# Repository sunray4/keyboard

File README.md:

# RayBoard

This custom iOS mechanical keyboard features:
- 95 switches in keyboard matrix
- 0.91" OLED display to indicate capslock and play simple animations
- Rotary Encoder Switch for volume/brightness control
- Self-designed 3D printed case (Fusion 360)
- Custom PCB (Kicad)
- KMK firmware
- Powered by Raspberry Pi Pico!!

## Video Demo
<a href="https://hc-cdn.hel1.your-objectstorage.com/s/v3/838ee69a4a7859cef761f4f2ce842302e564a838_rayboard_demo4.mp4" target="_blank">Demo Link</a>

## PCB
| **Schematic** |
|-----------|
||

| **PCB** |
|-----------|
||

| **3D Render** |
|-----------|
||
||

| **Case Design** |
|-----------|
||
||

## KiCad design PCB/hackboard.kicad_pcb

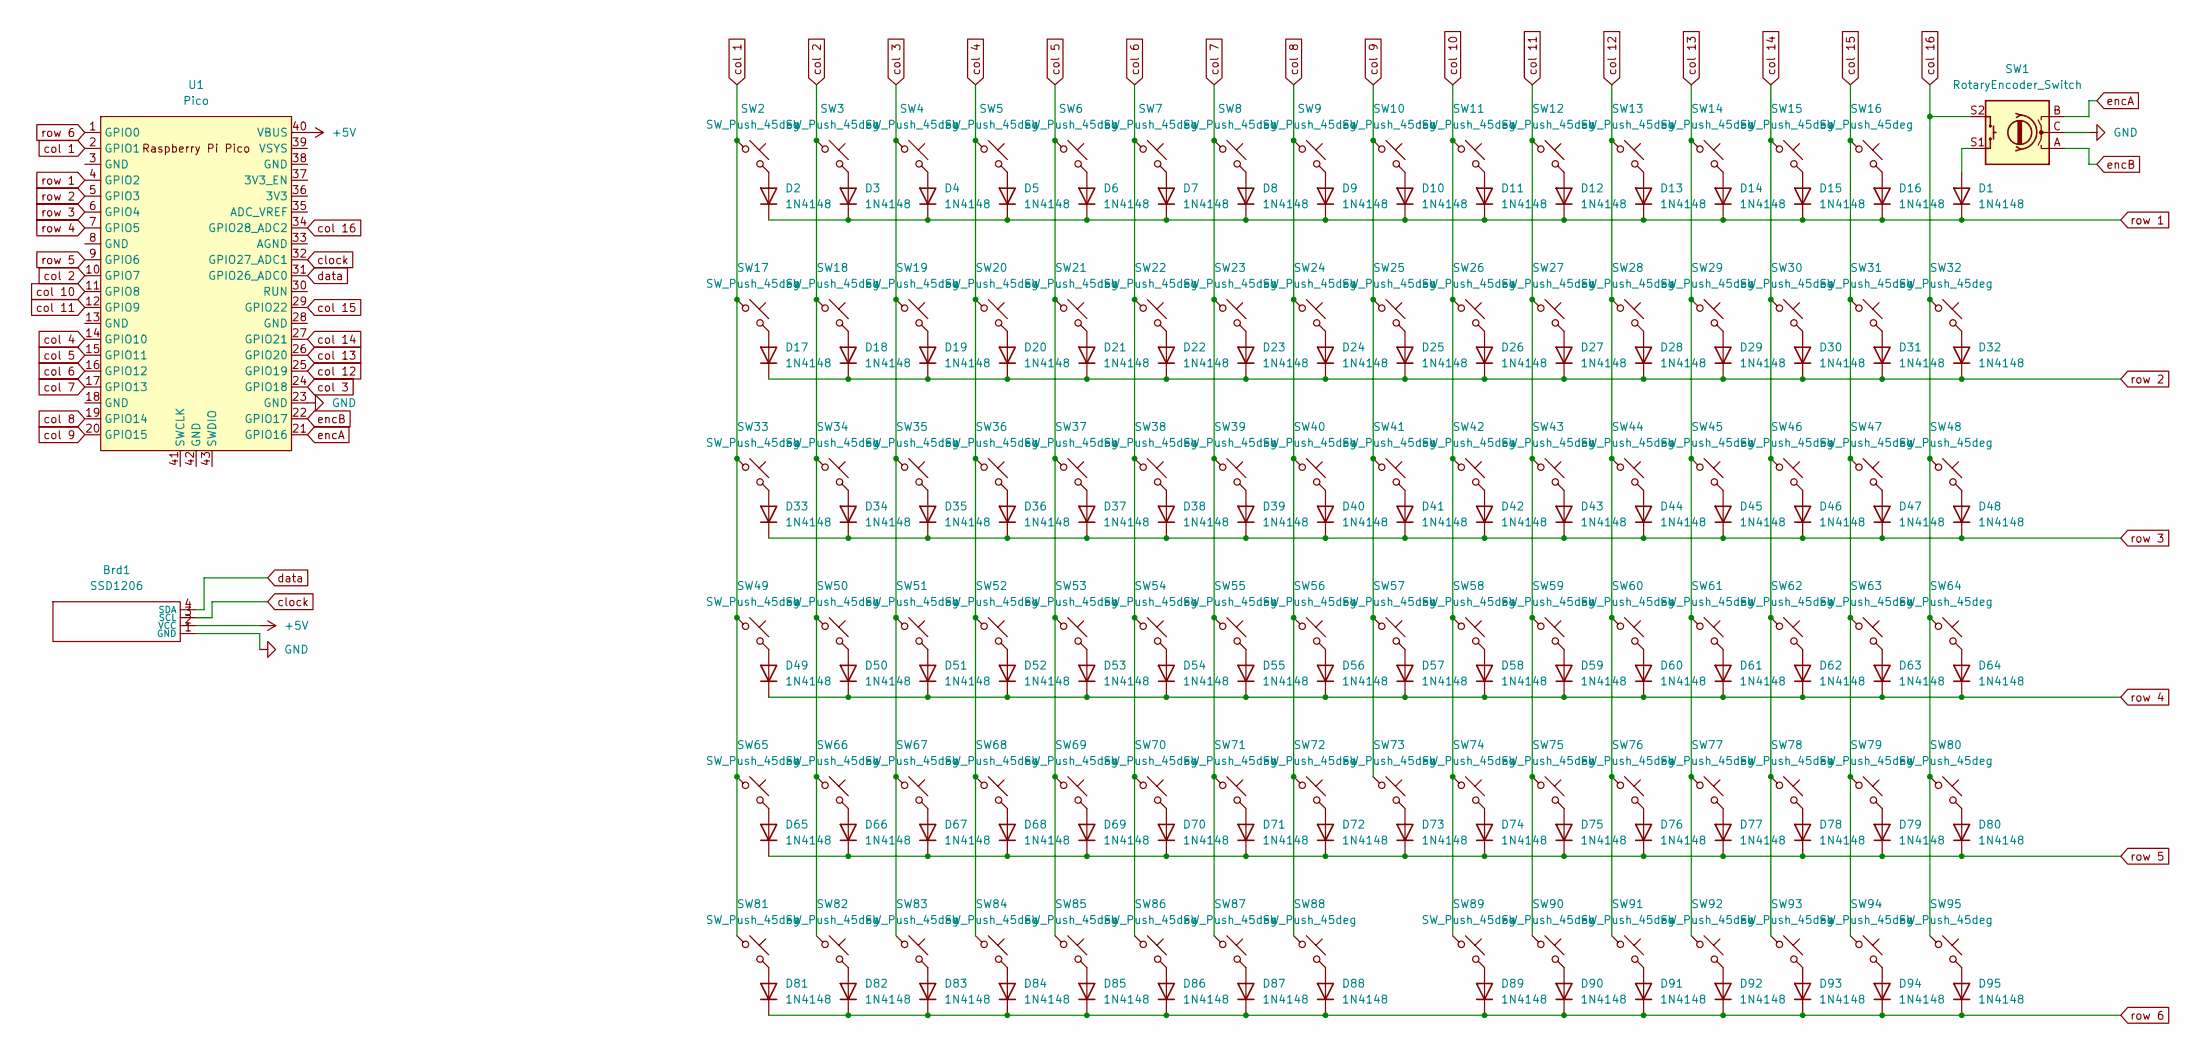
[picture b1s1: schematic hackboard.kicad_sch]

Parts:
Brd1: SSD1206; SSD1306-0.91-OLED-4pin-128x32
D1, D2, D3, D4, D5, D6, D7, D8, D9, D10, D11, D12, D13, D14, D15, D16, D17, D18, D19, D20, D21, D22, D23, D24, D25, D26, D27, D28, D29, D30, D31, D32, D33, D34, D35, D36, D37, D38, D39, D40, D41, D42, D43, D44, D45, D46, D47, D48, D49, D50, D51, D52, D53, D54, D55, D56, D57, D58, D59, D60, D61, D62, D63, D64, D65, D66, D67, D68, D69, D70, D71, D72, D73, D74, D75, D76, D77, D78, D79, D80, D81, D82, D83, D84, D85, D86, D87, D88, D89, D90, D91, D92, D93, D94, D95: 1N4148; D_SOD-123
SW1: RotaryEncoder_Switch; RotaryEncoder_Alps_EC11E-Switch_Vertical_H20mm
SW2, SW3, SW4, SW5, SW6, SW7, SW8, SW9, SW10, SW11, SW12, SW13, SW14, SW15, SW16, SW17, SW18, SW19, SW20, SW21, SW22, SW23, SW24, SW25, SW26, SW27, SW28, SW29, SW30, SW31, SW33, SW34, SW36, SW37, SW38, SW39, SW40, SW41, SW42, SW43, SW44, SW45, SW46, SW47, SW49, SW50, SW53, SW54, SW55, SW56, SW57, SW58, SW59, SW60, SW61, SW62, SW63, SW65, SW66, SW67, SW69, SW70, SW71, SW72, SW73, SW74, SW75, SW76, SW77, SW78, SW80, SW82, SW83, SW86, SW87, SW88, SW92, SW93, SW94, SW95: SW_Push_45deg; SW_Cherry_MX_1.00u_PCB
SW32, SW81: SW_Push_45deg; SW_Cherry_MX_2.00u_PCB
SW35, SW48: SW_Push_45deg; SW_Cherry_MX_1.50u_PCB
SW51, SW84: SW_Push_45deg; SW_Cherry_MX_2.00u_Vertical_PCB
SW52, SW79: SW_Push_45deg; SW_Cherry_MX_1.75u_PCB
SW64, SW68: SW_Push_45deg; SW_Cherry_MX_2.25u_PCB
SW85, SW90, SW91: SW_Push_45deg; SW_Cherry_MX_1.25u_PCB
SW89: SW_Push_45deg; SW_Cherry_MX_6.25u_PCB
U1: Pico; RaspberryPi_Pico_Common_THT

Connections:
+5V: Brd1.2 (VCC), U1.40 (VBUS)
GND: Brd1.1 (GND), SW1.C, U1.23 (GND)
unnamed: D1.2 (A), SW1.S1
unnamed: D2.2 (A), SW2.2
unnamed: D3.2 (A), SW3.2
unnamed: D4.2 (A), SW4.2
unnamed: D5.2 (A), SW5.2
unnamed: D6.2 (A), SW6.2
unnamed: D7.2 (A), SW7.2
unnamed: D8.2 (A), SW8.2
unnamed: D9.2 (A), SW9.2
unnamed: D10.2 (A), SW10.2
unnamed: D11.2 (A), SW11.2
unnamed: D12.2 (A), SW12.2
unnamed: D13.2 (A), SW13.2
unnamed: D14.2 (A), SW14.2
unnamed: D15.2 (A), SW15.2
unnamed: D16.2 (A), SW16.2
unnamed: D17.2 (A), SW17.2
unnamed: D18.2 (A), SW18.2
unnamed: D19.2 (A), SW19.2
unnamed: D20.2 (A), SW20.2
unnamed: D21.2 (A), SW21.2
unnamed: D22.2 (A), SW22.2
unnamed: D23.2 (A), SW23.2
unnamed: D24.2 (A), SW24.2
unnamed: D25.2 (A), SW25.2
unnamed: D26.2 (A), SW26.2
unnamed: D27.2 (A), SW27.2
unnamed: D28.2 (A), SW28.2
unnamed: D29.2 (A), SW29.2
unnamed: D30.2 (A), SW30.2
unnamed: D31.2 (A), SW31.2
unnamed: D32.2 (A), SW32.2
unnamed: D33.2 (A), SW33.2
unnamed: D34.2 (A), SW34.2
unnamed: D35.2 (A), SW35.2
unnamed: D36.2 (A), SW36.2
unnamed: D37.2 (A), SW37.2
unnamed: D38.2 (A), SW38.2
unnamed: D39.2 (A), SW39.2
unnamed: D40.2 (A), SW40.2
unnamed: D41.2 (A), SW41.2
unnamed: D42.2 (A), SW42.2
unnamed: D43.2 (A), SW43.2
unnamed: D44.2 (A), SW44.2
unnamed: D45.2 (A), SW45.2
unnamed: D46.2 (A), SW46.2
unnamed: D47.2 (A), SW47.2
unnamed: D48.2 (A), SW48.2
unnamed: D49.2 (A), SW49.2
unnamed: D50.2 (A), SW50.2
unnamed: D51.2 (A), SW51.2
unnamed: D52.2 (A), SW52.2
unnamed: D53.2 (A), SW53.2
unnamed: D54.2 (A), SW54.2
unnamed: D55.2 (A), SW55.2
unnamed: D56.2 (A), SW56.2
unnamed: D57.2 (A), SW57.2
unnamed: D58.2 (A), SW58.2
unnamed: D59.2 (A), SW59.2
unnamed: D60.2 (A), SW60.2
unnamed: D61.2 (A), SW61.2
unnamed: D62.2 (A), SW62.2
unnamed: D63.2 (A), SW63.2
unnamed: D64.2 (A), SW64.2
unnamed: D65.2 (A), SW65.2
unnamed: D66.2 (A), SW66.2
unnamed: D67.2 (A), SW67.2
unnamed: D68.2 (A), SW68.2
unnamed: D69.2 (A), SW69.2
unnamed: D70.2 (A), SW70.2
unnamed: D71.2 (A), SW71.2
unnamed: D72.2 (A), SW72.2
unnamed: D73.2 (A), SW73.2
unnamed: D74.2 (A), SW74.2
unnamed: D75.2 (A), SW75.2
unnamed: D76.2 (A), SW76.2
unnamed: D77.2 (A), SW77.2
unnamed: D78.2 (A), SW78.2
unnamed: D79.2 (A), SW79.2
unnamed: D80.2 (A), SW80.2
unnamed: D81.2 (A), SW81.2
unnamed: D82.2 (A), SW82.2
unnamed: D83.2 (A), SW83.2
unnamed: D84.2 (A), SW84.2
unnamed: D85.2 (A), SW85.2
unnamed: D86.2 (A), SW86.2
unnamed: D87.2 (A), SW87.2
unnamed: D88.2 (A), SW88.2
unnamed: D89.2 (A), SW89.2
unnamed: D90.2 (A), SW90.2
unnamed: D91.2 (A), SW91.2
unnamed: D92.2 (A), SW92.2
unnamed: D93.2 (A), SW93.2
unnamed: D94.2 (A), SW94.2
unnamed: D95.2 (A), SW95.2
clock: Brd1.3 (SCL), U1.32 (GPIO27_ADC1)
col 1: SW2.1, SW17.1, SW33.1, SW49.1, SW65.1, SW81.1, U1.2 (GPIO1)
col 2: SW3.1, SW18.1, SW34.1, SW50.1, SW66.1, SW82.1, U1.10 (GPIO7)
col 3: SW4.1, SW19.1, SW35.1, SW51.1, SW67.1, SW83.1, U1.24 (GPIO18)
col 4: SW5.1, SW20.1, SW36.1, SW52.1, SW68.1, SW84.1, U1.14 (GPIO10)
col 5: SW6.1, SW21.1, SW37.1, SW53.1, SW69.1, SW85.1, U1.15 (GPIO11)
col 6: SW7.1, SW22.1, SW38.1, SW54.1, SW70.1, SW86.1, U1.16 (GPIO12)
col 7: SW8.1, SW23.1, SW39.1, SW55.1, SW71.1, SW87.1, U1.17 (GPIO13)
col 8: SW9.1, SW24.1, SW40.1, SW56.1, SW72.1, SW88.1, U1.19 (GPIO14)
col 9: SW10.1, SW25.1, SW41.1, SW57.1, SW73.1, U1.20 (GPIO15)
col 10: SW11.1, SW26.1, SW42.1, SW58.1, SW74.1, SW89.1, U1.11 (GPIO8)
col 11: SW12.1, SW27.1, SW43.1, SW59.1, SW75.1, SW90.1, U1.12 (GPIO9)
col 12: SW13.1, SW28.1, SW44.1, SW60.1, SW76.1, SW91.1, U1.25 (GPIO19)
col 13: SW14.1, SW29.1, SW45.1, SW61.1, SW77.1, SW92.1, U1.26 (GPIO20)
col 14: SW15.1, SW30.1, SW46.1, SW62.1, SW78.1, SW93.1, U1.27 (GPIO21)
col 15: SW16.1, SW31.1, SW47.1, SW63.1, SW79.1, SW94.1, U1.29 (GPIO22)
col 16: SW1.S2, SW32.1, SW48.1, SW64.1, SW80.1, SW95.1, U1.34 (GPIO28_ADC2)
data: Brd1.4 (SDA), U1.31 (GPIO26_ADC0)
encA: SW1.B, U1.21 (GPIO16)
encB: SW1.A, U1.22 (GPIO17)
row 1: D1.1 (K), D2.1 (K), D3.1 (K), D4.1 (K), D5.1 (K), D6.1 (K), D7.1 (K), D8.1 (K), D9.1 (K), D10.1 (K), D11.1 (K), D12.1 (K), D13.1 (K), D14.1 (K), D15.1 (K), D16.1 (K), U1.4 (GPIO2)
row 2: D17.1 (K), D18.1 (K), D19.1 (K), D20.1 (K), D21.1 (K), D22.1 (K), D23.1 (K), D24.1 (K), D25.1 (K), D26.1 (K), D27.1 (K), D28.1 (K), D29.1 (K), D30.1 (K), D31.1 (K), D32.1 (K), U1.5 (GPIO3)
row 3: D33.1 (K), D34.1 (K), D35.1 (K), D36.1 (K), D37.1 (K), D38.1 (K), D39.1 (K), D40.1 (K), D41.1 (K), D42.1 (K), D43.1 (K), D44.1 (K), D45.1 (K), D46.1 (K), D47.1 (K), D48.1 (K), U1.6 (GPIO4)
row 4: D49.1 (K), D50.1 (K), D51.1 (K), D52.1 (K), D53.1 (K), D54.1 (K), D55.1 (K), D56.1 (K), D57.1 (K), D58.1 (K), D59.1 (K), D60.1 (K), D61.1 (K), D62.1 (K), D63.1 (K), D64.1 (K), U1.7 (GPIO5)
row 5: D65.1 (K), D66.1 (K), D67.1 (K), D68.1 (K), D69.1 (K), D70.1 (K), D71.1 (K), D72.1 (K), D73.1 (K), D74.1 (K), D75.1 (K), D76.1 (K), D77.1 (K), D78.1 (K), D79.1 (K), D80.1 (K), U1.9 (GPIO6)
row 6: D81.1 (K), D82.1 (K), D83.1 (K), D84.1 (K), D85.1 (K), D86.1 (K), D87.1 (K), D88.1 (K), D89.1 (K), D90.1 (K), D91.1 (K), D92.1 (K), D93.1 (K), D94.1 (K), D95.1 (K), U1.1 (GPIO0)

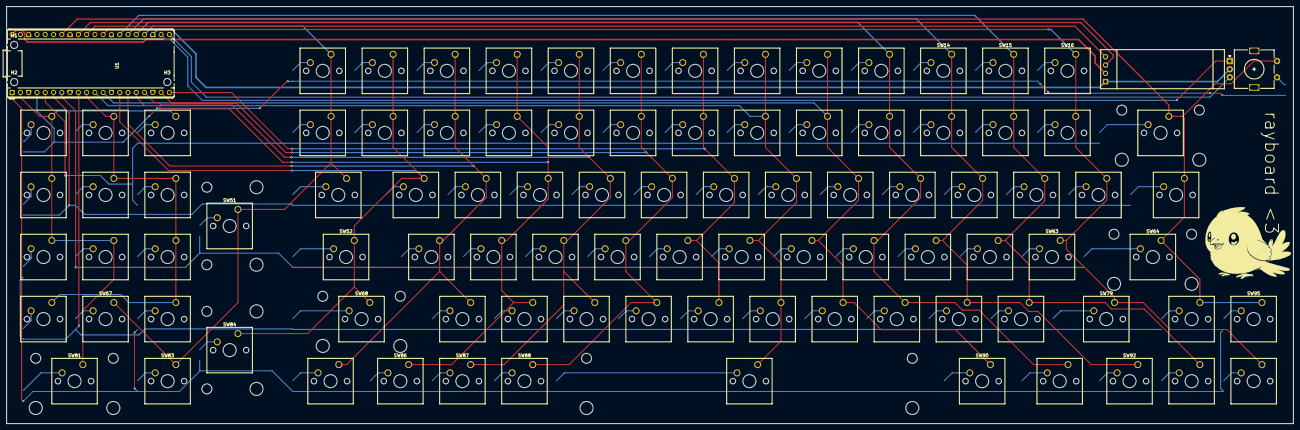
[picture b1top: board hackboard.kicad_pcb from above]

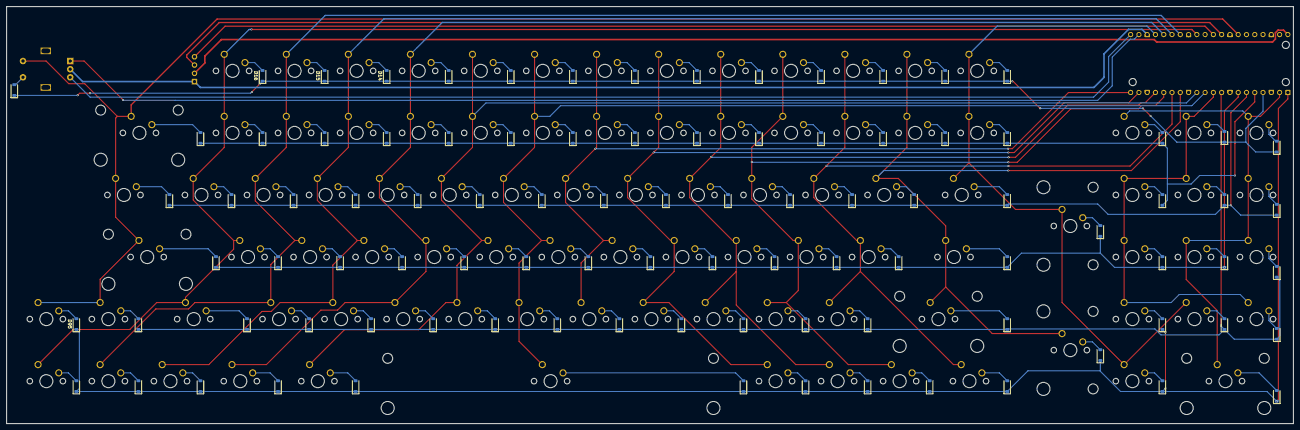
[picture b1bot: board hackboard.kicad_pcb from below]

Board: 2 copper layers, 395.0 x 128.0 mm, 195 parts (95 on the bottom side), 123 nets.

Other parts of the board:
H1, H2, H3: MountingHole; MountingHole_2.2mm_M2_DIN965

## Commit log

2025-05-31 completed keyboard - update firmware, add cad & production files
2025-05-31 add assembled keyboard image
2025-05-31 change assembled keyboard image
2025-05-31 add GIT ADD macro
2025-06-02 keycode change
